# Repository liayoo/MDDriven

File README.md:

Ionic App Base
=====================

A starting project for Ionic that optionally supports using custom SCSS.

## Using this project

We recommend using the [Ionic CLI](https://github.com/driftyco/ionic-cli) to create new Ionic projects that are based on this project but use a ready-made starter template.

For example, to start a new Ionic project with the default tabs interface, make sure the `ionic` utility is installed:

```bash
$ npm install -g ionic
```

Then run: 

```bash
$ ionic start myProject tabs
```

More info on this can be found on the Ionic [Getting Started](http://ionicframework.com/getting-started) page and the [Ionic CLI](https://github.com/driftyco/ionic-cli) repo.

## Issues
Issues have been disabled on this repo, if you do find an issue or have a question consider posting it on the [Ionic Forum](http://forum.ionicframework.com/).  Or else if there is truly an error, follow our guidelines for [submitting an issue](http://ionicframework.com/submit-issue/) to the main Ionic repository.
# MDDriven

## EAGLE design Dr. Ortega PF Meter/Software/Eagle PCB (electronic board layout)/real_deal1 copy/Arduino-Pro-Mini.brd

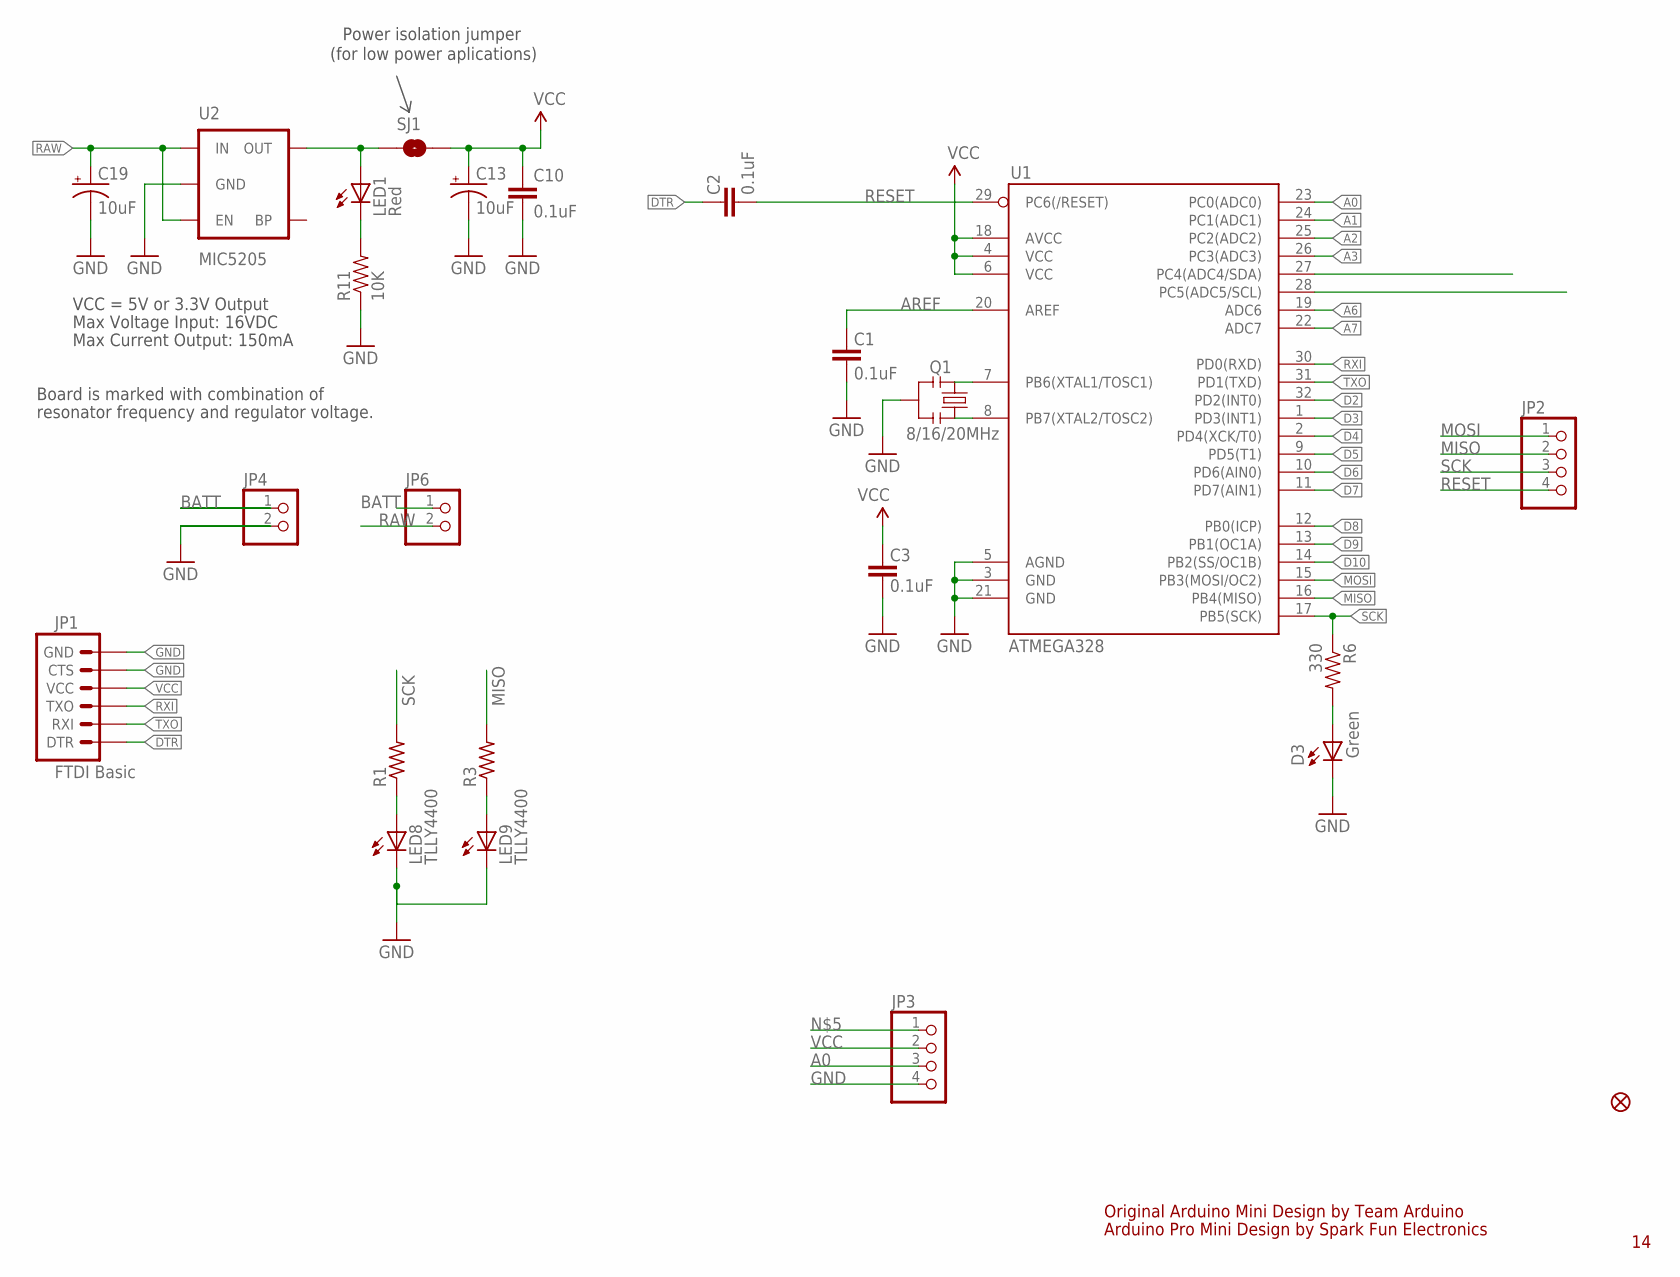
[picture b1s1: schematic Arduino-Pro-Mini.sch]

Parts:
C1, C2, C3, C10: 0.1uF; 0603-CAP
C13, C19: 10uF; EIA3216
D3: Green; 0603-LED-ALT1
JP1: FTDI Basic; 1X06
JP2, JP3: PINHD-1X4; 1X04
JP4, JP6: PINHD-1X2; 1X02
JP5: FIDUCIALUFIDUCIAL; MICRO-FIDUCIAL
LED1: Red; 0603-LED-ALT1
LED8, LED9: TLLY4400; LED3MM
Q1: 8/16/20MHz; RESONATOR-SMD-1:1
R1, R3: R-US_R0603; R0603
R6: 330; 0603-RES
R11: 10K; 0603-RES
SJ1: SOLDERJUMPERNC; SJ_2S
U1: ATMEGA328; TQFP32-08
U2: MIC5205; SOT23-5

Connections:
A0: JP3.3, U1.23 (PC0(ADC0))
A1: U1.24 (PC1(ADC1))
A2: U1.25 (PC2(ADC2))
A3: U1.26 (PC3(ADC3))
A4: U1.27 (PC4(ADC4/SDA))
A5: U1.28 (PC5(ADC5/SCL))
A6: U1.19 (ADC6)
A7: U1.22 (ADC7)
AREF: C1.2, U1.20 (AREF)
BATT: JP4.1, JP6.1
D2: U1.32 (PD2(INT0))
D3: U1.1 (PD3(INT1))
D4: U1.2 (PD4(XCK/T0))
D5: U1.9 (PD5(T1))
D6: U1.10 (PD6(AIN0))
D7: U1.11 (PD7(AIN1))
D8: U1.12 (PB0(ICP))
D9: U1.13 (PB1(OC1A))
D10: U1.14 (PB2(SS/OC1B))
DTR: C2.2, JP1.1 (DTR)
GND: C1.1, C3.1, C10.2, C13.C (-), C19.C (-), D3.C, JP1.5 (CTS), JP1.6 (GND), JP3.4, JP4.2, LED8.K (C), LED9.K (C), Q1.2, R11.1, U1.3 (GND), U1.5 (AGND), U1.21 (GND), U2.2 (GND)
MISO: JP2.2, R3.2, U1.16 (PB4(MISO))
MOSI: JP2.1, U1.15 (PB3(MOSI/OC2))
unnamed: Q1.3, U1.8 (PB7(XTAL2/TOSC2))
unnamed: Q1.1, U1.7 (PB6(XTAL1/TOSC1))
unnamed: LED1.A, SJ1.1, U2.5 (OUT)
unnamed: LED1.C, R11.2
unnamed: D3.A, R6.2
unnamed: LED8.A, R1.1
unnamed: LED9.A, R3.1
RAW: C19.A (+), JP6.2, U2.1 (IN), U2.3 (EN)
RESET: C2.1, JP2.4, U1.29 (PC6(/RESET))
RXI: JP1.3 (TXO), U1.30 (PD0(RXD))
SCK: JP2.3, R1.2, R6.1, U1.17 (PB5(SCK))
TXO: JP1.2 (RXI), U1.31 (PD1(TXD))
VCC: C3.2, C10.1, C13.A (+), JP1.4 (VCC), JP3.2, SJ1.2, U1.4 (VCC), U1.6 (VCC), U1.18 (AVCC)

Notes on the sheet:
Original Arduino Mini Design by Team Arduino
Arduino Pro Mini Design by Spark Fun Electronics
Max Voltage Input: 16VDC
Max Current Output: 150mA
Board is marked with combination of
resonator frequency and regulator voltage.
VCC = 5V or 3.3V Output
Power isolation jumper
(for low power aplications)

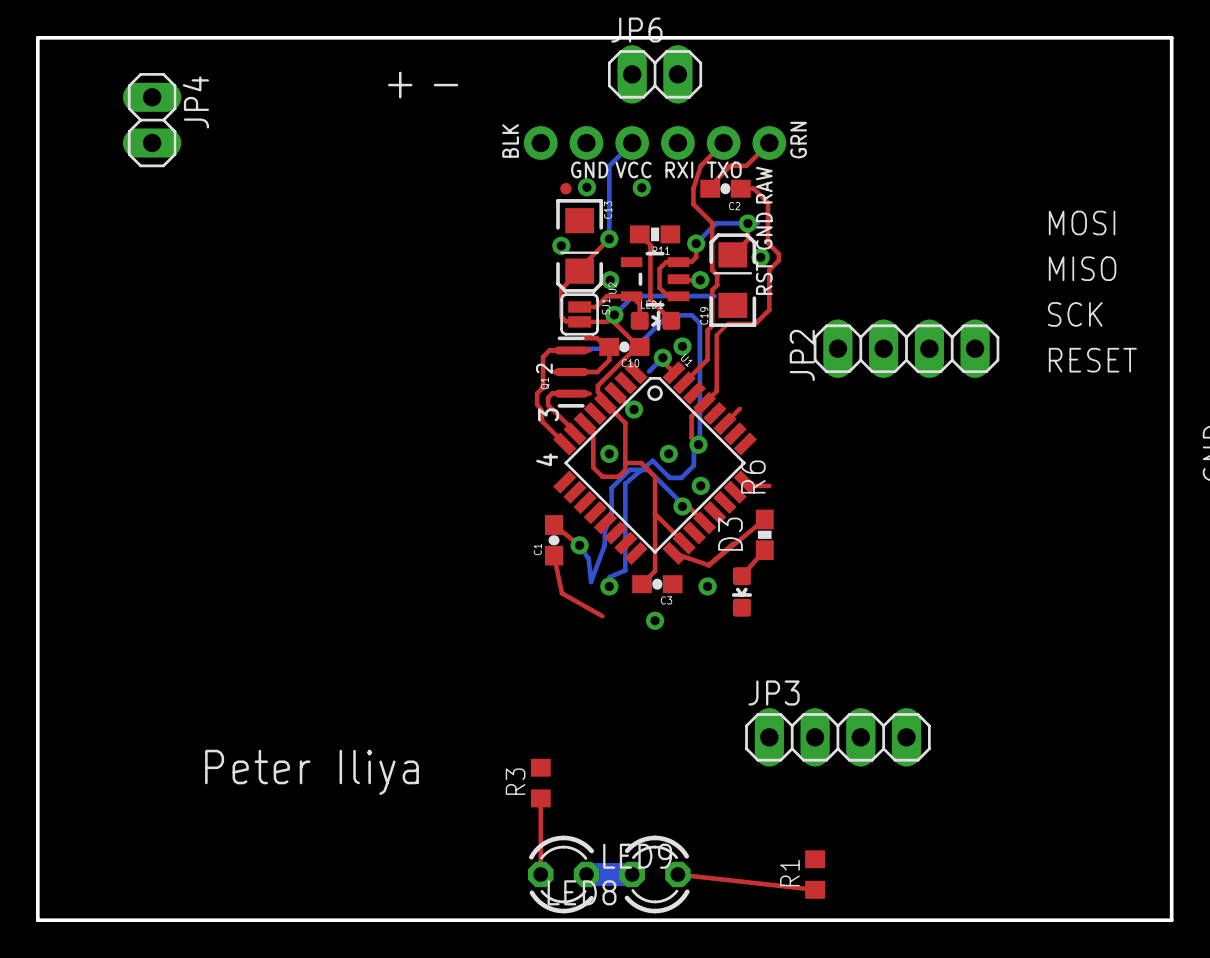
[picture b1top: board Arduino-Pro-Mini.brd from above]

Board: 2 copper layers, 63.0 x 49.0 mm, 24 parts (1 on the bottom side), 20 nets.

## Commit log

2016-09-25 committing existing files
2016-10-01 changes to some app details

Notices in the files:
parts and their libraries:
SparkFun-Passives: Licensing: CC v3.0 Share-Alike You are welcome to use this library for commercial purposes.
